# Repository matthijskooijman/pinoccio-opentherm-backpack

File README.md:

Pinoccio Scout Opentherm backpack
=================================

This repository contains the schematics and board design for a backpack
(expansion board) that allows a Pinoccio Scout to communicate with a
boiler using the Opentherm protocol.

This only implements the master side of the Opentherm protocol, allowing
a connection to a single slave (boiler). The hardware design is based on
a part of the [Opentherm gateway][1]. In addition to an Opentherm
connection, this also contains a second screw terminal intended to
connect an existing on/off thermostat.

[1]: http://otgw.tclcode.com/

The board design has been optimized for a single-layer PCB, in order to
allow milling the board on a CNC mill. The front copper layer is used in
the board design, but the traces are only straight and the vias are
extra big, to allow using wire bridges instead of proper traces on the
front.

License
-------
This hardware design is created by Matthijs Kooijman and Bas Peschier.
It is made available under the [Creative Commons Zero 1.0
universal license][CC0].

[CC0]: https://creativecommons.org/publicdomain/zero/1.0/legalcode

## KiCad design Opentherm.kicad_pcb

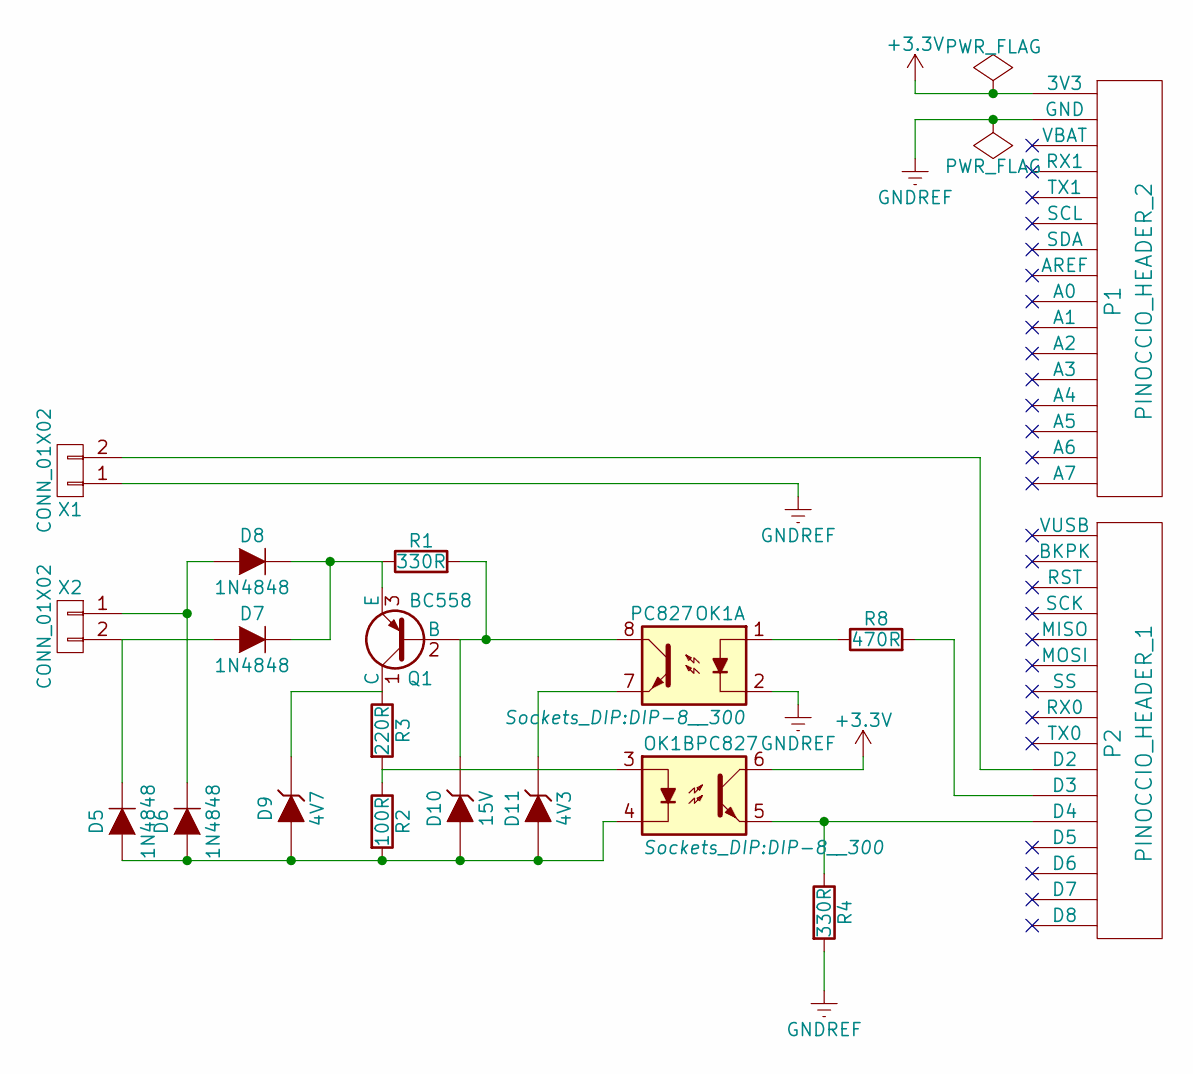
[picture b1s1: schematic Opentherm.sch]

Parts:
D5, D6, D7, D8: 1N4848; D3
D9: 4V7; D3
D10: 15V; D3
D11: 4V3; D3
OK1: PC827; DIP-8__300
P1: PINOCCIO_HEADER_2; Pinoccio-Header
P2: PINOCCIO_HEADER_1; Pinoccio-Header
Q1: BC558; TO-92_Molded_Wide
R1, R4: 330R; R3
R2: 100R; R4
R3: 220R; R3
R8: 470R; R4
X1, X2: CONN_01X02; bornier2

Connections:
+3V3: OK1.6, P1.1 (3V3)
GNDREF: OK1.2, P1.2 (GND), R4.2, X1.1
unnamed: D5.2 (K), D7.1 (A), X2.2
unnamed: D6.2 (K), D8.1 (A), X2.1
unnamed: D7.2 (K), D8.2 (K), Q1.3 (E), R1.1
unnamed: D9.2 (K), Q1.1 (C), R3.1
unnamed: D5.1 (A), D6.1 (A), D9.1 (A), D10.1 (A), D11.1 (A), OK1.4, R2.2
unnamed: D10.2 (K), OK1.8, Q1.2 (B), R1.2
unnamed: D11.2 (K), OK1.7
unnamed: OK1.1, R8.1
unnamed: OK1.3, R2.1, R3.2
unnamed: OK1.5, P2.12 (D4), R4.1
unnamed: P2.10 (D2), X1.2
unnamed: P2.11 (D3), R8.2

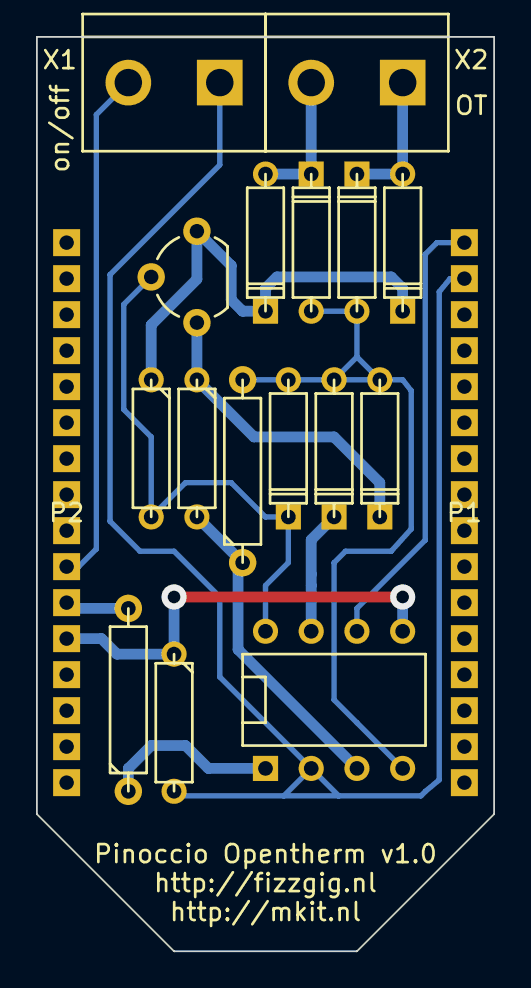
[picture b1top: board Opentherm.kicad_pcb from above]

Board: 2 copper layers, 25.4 x 50.8 mm, 18 parts (0 on the bottom side), 14 nets.

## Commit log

2015-04-08 Initial empty commit
2015-04-08 Add initial version
    This adds the project file, schematic and pcb. The cache.lib file is
    added, since that conveniently contains all the needed footprints,
    regardless of their original source. The other files are temporary or
    indirectly generated, so left out.
2015-04-08 Add .gitignore for temporary files
2015-04-08 Add README
